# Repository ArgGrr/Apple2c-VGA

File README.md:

# Apple2cVGA

I have a PAL Apple 2c which does not produce colour on the composite output.
I made this project to learn about FPGAs and generate a nice VGA image from the Apple 2c video expansion port.

Supports:
- 40 & 80 column text in white. This includes the text in mixed graphics + text modes.
- GR & DGR colours
- HGR colours
- DHGR colours, including AppleWin-like sub-pixel rendering.

It is probably just easier to say it supports pixel accurate video output, but where text mode is drawn monochrome by default.

Various rendering modes, including:

0.  Monochrome (white)
1.  Monochrome (green)
2.  CREF mode
3.  140x192 resolution
4.  580x192 16 Colours no white text
5.  580x192 16 Colours, white text in tex/mixed mode. Default.
6.  Test pattern
7.  Monitor alignment pattern

Brief outline of how it works:
1. Track the A2 blanking signal, detect the horizontal and vertical blanking pulses, use in conjunction with 14MHZ clock to figure out horizontal pixel and vertical line counters.
2. Store the SERDATA bits in groups of 4, aligned to the CREF cycle, into the block RAM. Additionally, store the value of !GR at the start of each line, to determine if the line is TEXT or graphics mode.
3. Generate in a VGA sync module running from the VGA clock, horizontal pixel and vertical line counters.
4. Draw the data from the block RAM, depending on the rendering mode selected. Renders a 580 x 382 image, whith some padding before and after each line, and doubling the lines, onto a 640x480 VGA screen.

Verilog project done in [IceStudio](https://icestudio.io/).

Parts required:
- TinyFPGA BX
- 5v to 3v3  4 channel logic line level converter
- 12v to 5v regulator
- VGA pixel clock resonator, 25Mhz or there abouts. Better if it runs from 3.3v, otherwise you will need to route it through logic level converter.
- Bunch of resistors for the colour "DAC"
- Push button to change rendering mode

My design draws less than 30mA from the 12v line from the expansion port.

Points of interest:
- The NTSC Colourburst is aligned to the blanking output from the machine. Even though HGR and DHGR lines start at different times due to the different pixel clocks, if you count from the unblanking, you can infer the pixel colour later on. Therefore we don't need to store any CREF information in the block RAM.
- CREF rendering mode demonstrates this. Squint at it and the colours sort of match.
- By drawing DHGR 560x192 correctly, you get GR and HGR rendering for free.
- The sub pixel rendering mode is very close if not 100% the same as the Apple2 Win emulator, but I have no hardware (RGB Monitor etc) to reference it against.
- Because the Apple 2 TEXT or GRAPHICS mode is stored per line, things like Crazy Cycles 2c do not look exactly the same as a real machine. I.e. if it is drawing a small TEXT section at the start of a line, the whole line will be drawn black & white. This is an extreme case and I can live with it.
- The 140x192 rendering mode is bugged, the edges of the frame bleed out to the edges of the screen.
- 80col text is only really readable when rendered white / monochrome because of the sub pixel rendering mode, no doubt the same situations occur with a monitor.

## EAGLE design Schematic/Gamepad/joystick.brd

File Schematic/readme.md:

LibrePCB Schematic project. Work in progress.

Ports have swapped while I figure out the best layout.

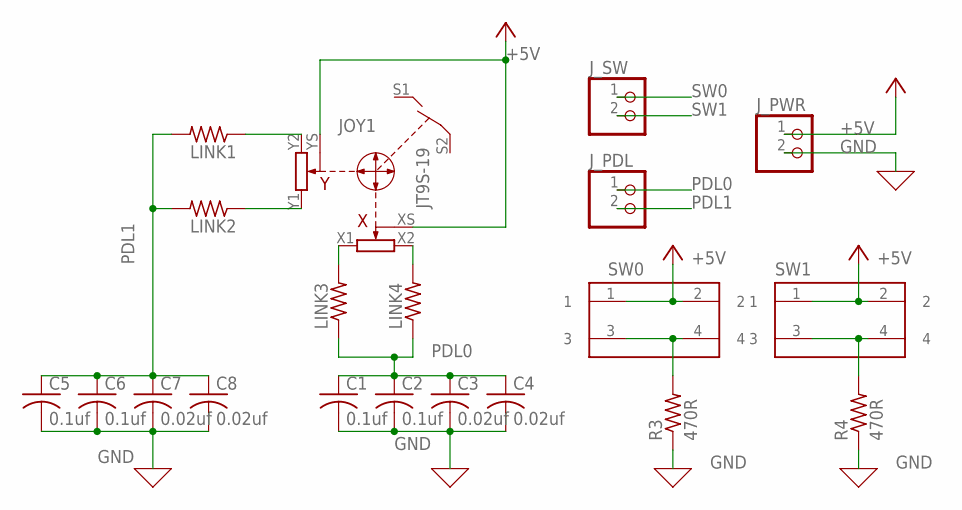
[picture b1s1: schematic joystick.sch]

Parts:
C1, C2, C5, C6: 0.1uf; C0805
C3, C4, C7, C8: 0.02uf; C0805
JOY1: JT9S-19; JT9S-1P
J_PDL: PINHD-1X2; 1X02
J_PWR: PINHD-1X2; 1X02
J_SW: PINHD-1X2; 1X02
LINK1, LINK2, LINK3, LINK4: 0; R0805
R3, R4: 470R; R0805
SW0, SW1: 430476073716

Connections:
+5V: JOY1.XS, JOY1.YS, J_PWR.1, SW0.1, SW0.2, SW1.1, SW1.2
GND: C1.2, C2.2, C3.2, C4.2, C5.2, C6.2, C7.2, C8.2, J_PWR.2, R3.1, R4.1
unnamed: JOY1.X1, LINK3.2
unnamed: JOY1.X2, LINK4.2
unnamed: JOY1.Y1, LINK2.1
unnamed: JOY1.Y2, LINK1.1
PDL0: C1.1, C2.1, C3.1, C4.1, J_PDL.1, LINK3.1, LINK4.1
PDL1: C5.1, C6.1, C7.1, C8.1, J_PDL.2, LINK1.2, LINK2.2
SW0: J_SW.1, R3.2, SW0.3, SW0.4
SW1: J_SW.2, R4.2, SW1.3, SW1.4

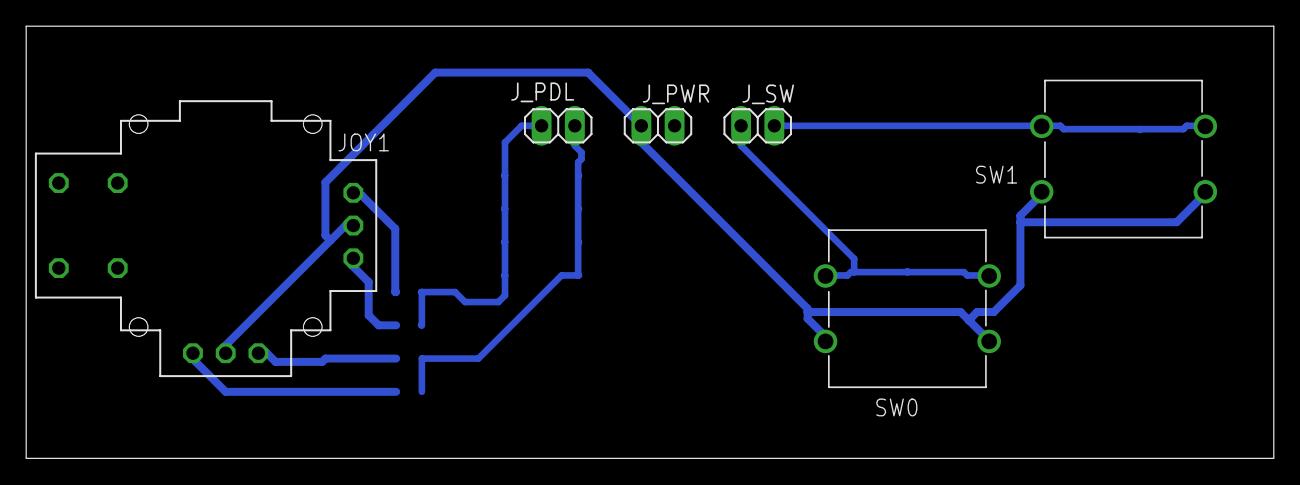
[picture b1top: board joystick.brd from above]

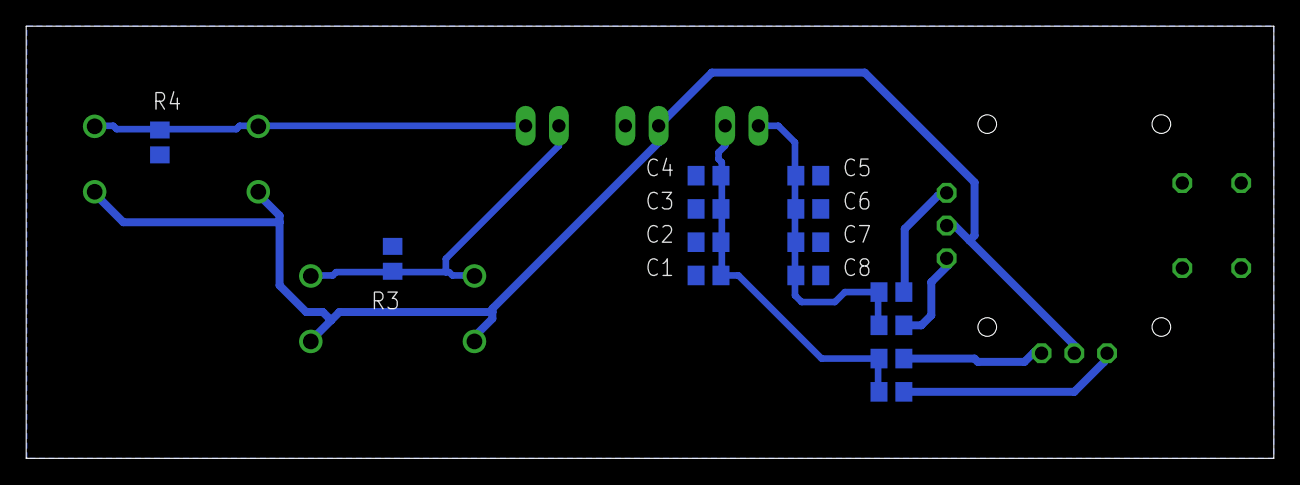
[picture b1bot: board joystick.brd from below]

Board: 2 copper layers, 95.3 x 33.0 mm, 20 parts (14 on the bottom side), 10 nets.

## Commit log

2020-02-16 :tada: Added .gitattributes
2020-02-16 v1
    Initial dump of v1 files.
2020-02-16 Add vb project
    Add VB project which collapses all 4096 sub pixel rendering cases down
    to ~159 unique options.
2020-02-16 Create LICENSE
2020-02-16 Add some happy snaps
2020-02-16 Schematic Libraries
2020-02-18 Add 3d models
2020-02-23 Schematic, 3d model updates
    Semi-finalised the schematic. Pending parts on order and attempted build.
    Working on 3d model for DB19 plug for disk drive port, sd card project.
2020-02-24 Case
    Started building a case, pending first build of the board of course.
2020-02-26 Adding standalone reset button cap
2020-02-28 Updated mode button.
2020-03-02 working on case
2020-03-04 Working on case for smartport sd device
2020-03-09 Various updates
2020-06-28 First PCB and build done, reworking.
    Built first version, had some issues. Reworking the PCB design in KiCAD. FPGA tweaked slightly to fix a colour bug and to remap IO.
2020-06-28 Added some video captures.
    I don't have a capture, took these with my phone, cropped and recompressed.
2020-06-28 Tidy up
2020-07-12 test

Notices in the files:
parts and their libraries:
Wurth_Elektronik_Electromechanic_Switch_: Copyright: Würth Elektronik
